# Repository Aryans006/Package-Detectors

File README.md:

A single layer pcb for a detector circuit, to be fabricated using ferric chloride etching

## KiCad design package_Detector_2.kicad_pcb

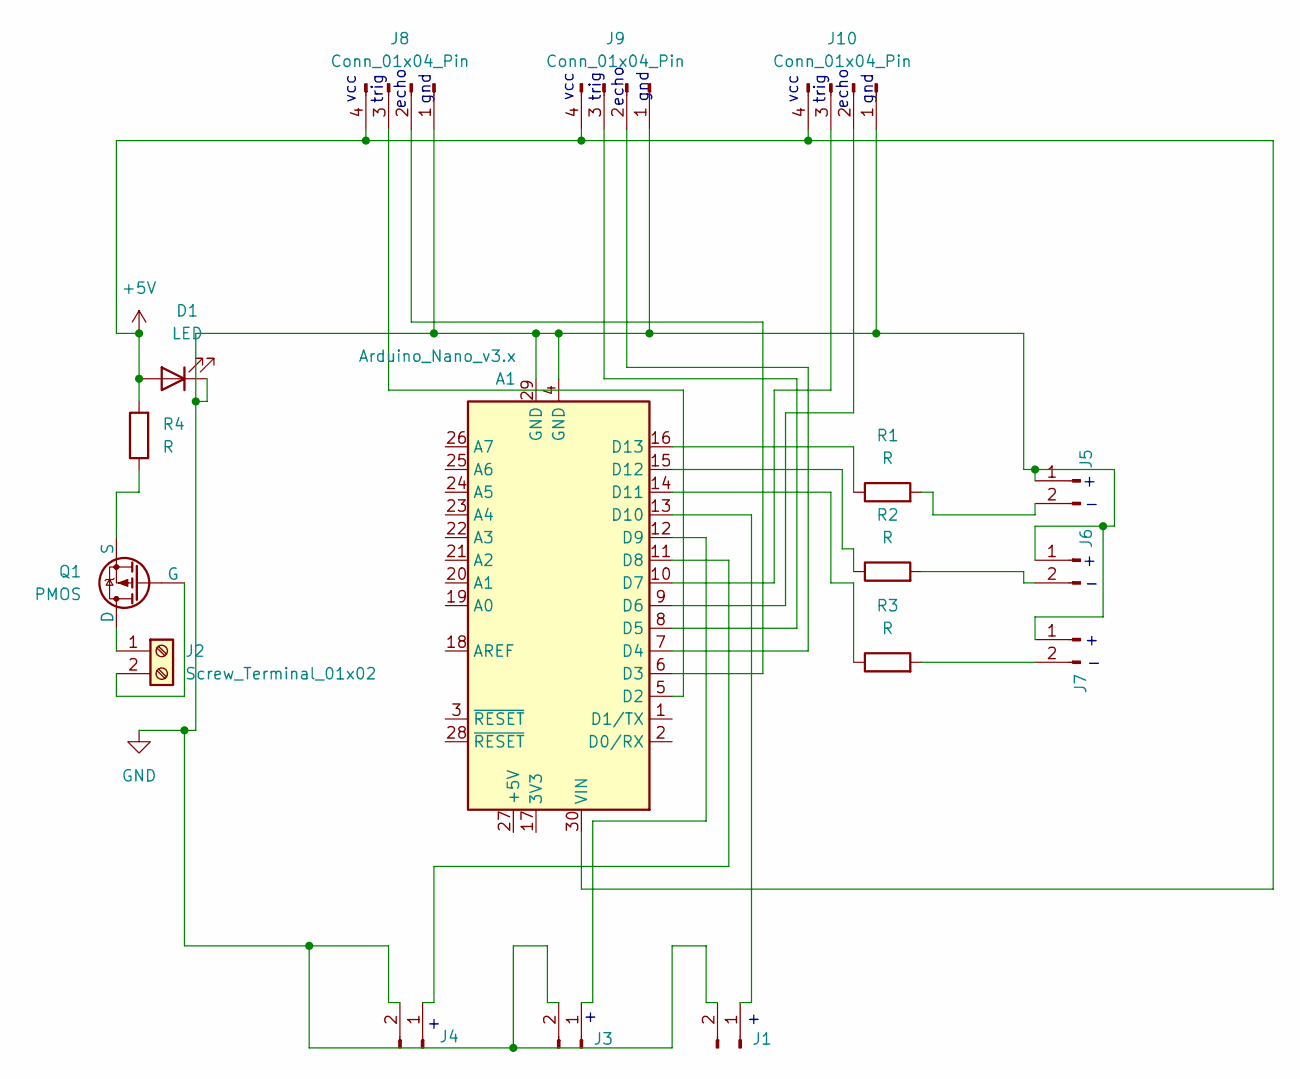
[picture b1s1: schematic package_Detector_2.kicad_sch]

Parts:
A1: Arduino_Nano_v3.x; Arduino_Nano
D1: LED; LED_D2.0mm_W4.8mm_H2.5mm_FlatTop
J1, J3, J4, J5, J6, J7: Conn_01x02_Pin
J2: Screw_Terminal_01x02; TerminalBlock_Xinya_XY308-2.54-2P_1x02_P2.54mm_Horizontal
J8, J9, J10: Conn_01x04_Pin; JST_EH_B6B-EH-A_1x06_P2.50mm_Vertical
Q1: PMOS; TO254P1054X469X1930-3
R1, R2, R3, R4: R; R_Axial_DIN0204_L3.6mm_D1.6mm_P7.62mm_Horizontal

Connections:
+5V: A1.30 (VIN), D1.2 (A), J8.4, J9.4, J10.4, R4.2
GND: A1.4 (GND), A1.29 (GND), D1.1 (K), J1.2, J3.2, J4.2, J5.1, J6.1, J7.1, J8.1, J9.1, J10.1
unnamed: A1.5 (D2), J8.3
unnamed: A1.6 (D3), J8.2
unnamed: A1.7 (D4), J9.2
unnamed: A1.8 (D5), J9.3
unnamed: A1.9 (D6), J10.2
unnamed: A1.10 (D7), J10.3
unnamed: A1.11 (D8), J4.1
unnamed: A1.12 (D9), J3.1
unnamed: A1.13 (D10), J1.1
unnamed: A1.14 (D11), R3.1
unnamed: A1.15 (D12), R2.1
unnamed: A1.16 (D13), R1.1
unnamed: J2.1, Q1.1 (D)
unnamed: J2.2, Q1.2 (G)
unnamed: J5.2, R1.2
unnamed: J6.2, R2.2
unnamed: J7.2, R3.2
unnamed: Q1.3 (S), R4.1

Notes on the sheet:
gnd
trig
echo
vcc

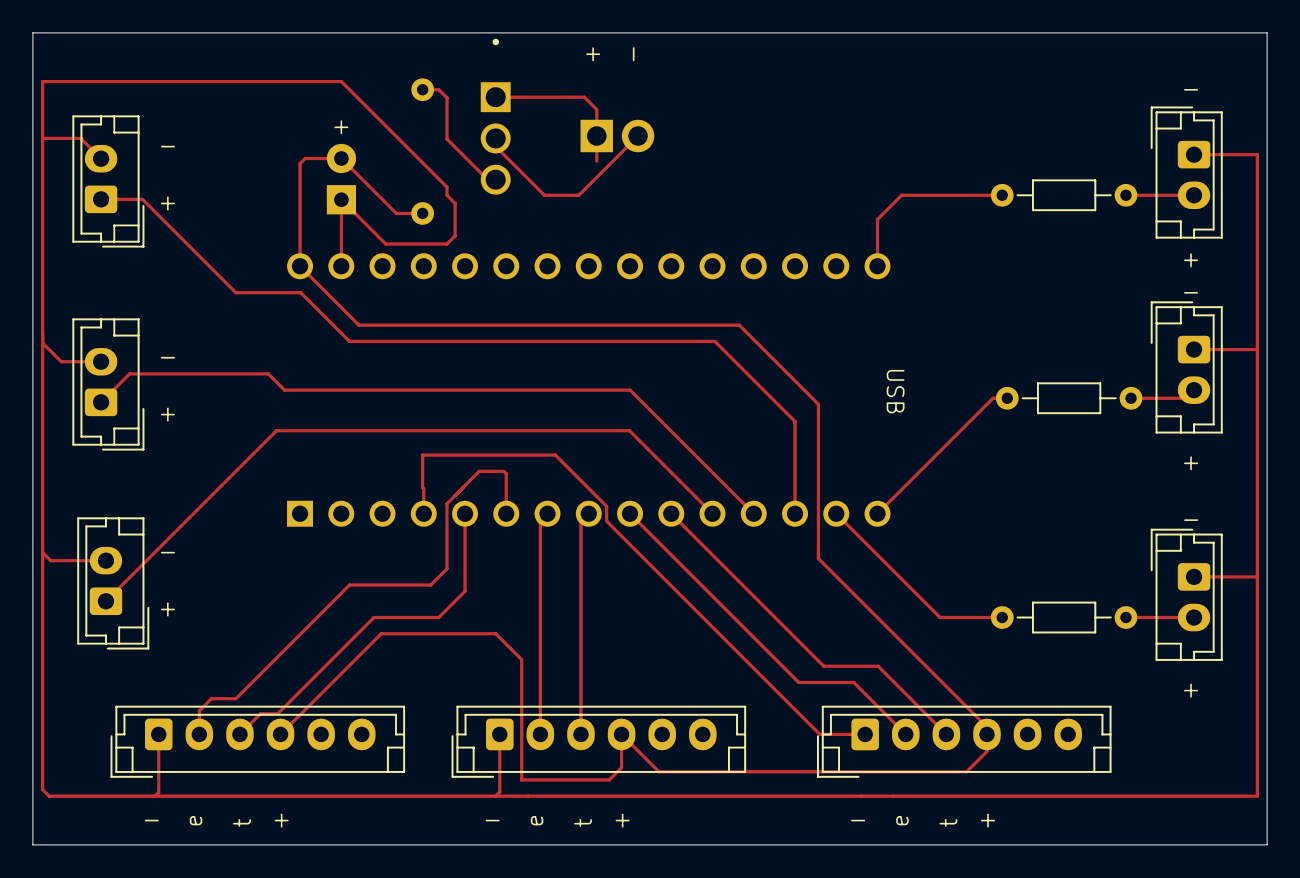
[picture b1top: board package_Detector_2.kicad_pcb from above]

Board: 2 copper layers, 76.0 x 50.0 mm, 17 parts (0 on the bottom side), 20 nets.

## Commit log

2025-01-10 added files
